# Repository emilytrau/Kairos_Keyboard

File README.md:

# Kairos_Keyboard
60% keyboard with MX-ALPS support and maximum compatability

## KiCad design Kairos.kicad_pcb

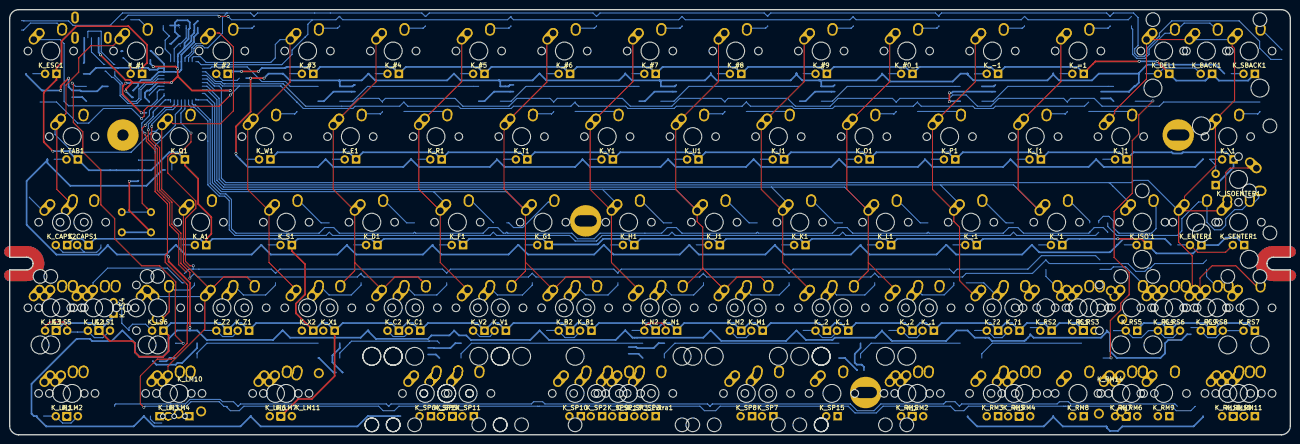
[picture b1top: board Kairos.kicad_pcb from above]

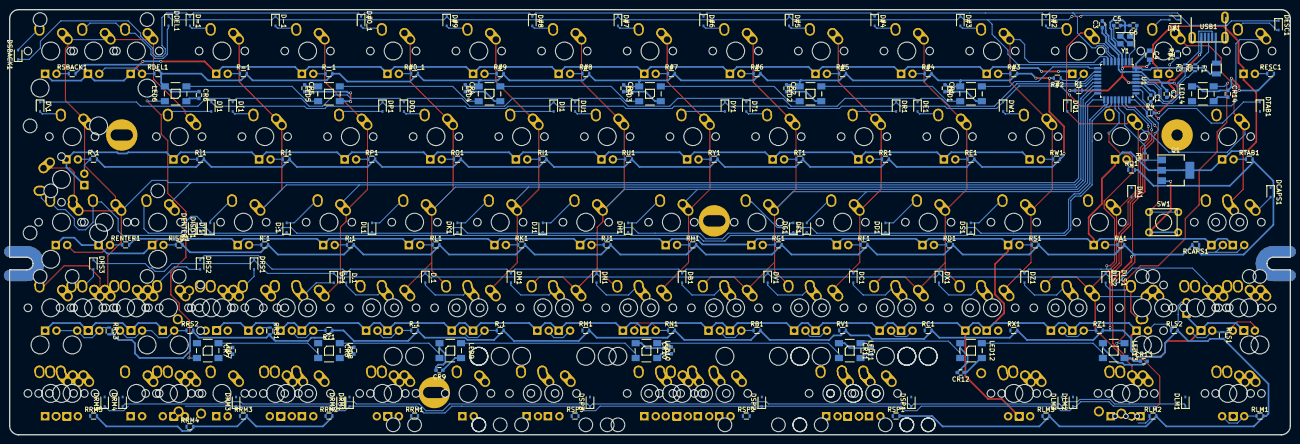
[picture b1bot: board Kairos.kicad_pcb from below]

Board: 2 copper layers, 285.0 x 94.6 mm, 300 parts (183 on the bottom side), 185 nets.

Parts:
C1: 1uF; C_0603
C2, C3: 100nF; C_0603
C4: 4.7uF; C_0805
C5, C6: 22pF; C_0603
CR1, CR2, CR3, CR4, CR5, CR6, CR7, CR8, CR9, CR10, CR11, CR12, CR13, CR14: 100nF; C_0603
D#0_1, D#1, D#2, D#3, D#4, D#5, D#6, D#7, D#8, D#9: 1N4148WS; D_SOD-323
D'1: 1N4148WS; D_SOD-323
D,1: 1N4148WS; D_SOD-323
D-1: 1N4148WS; D_SOD-323
D.1: 1N4148WS; D_SOD-323
D;1: 1N4148WS; D_SOD-323
D=1: 1N4148WS; D_SOD-323
D?1: 1N4148WS; D_SOD-323
DA1: 1N4148WS; D_SOD-323
DB1: 1N4148WS; D_SOD-323
DC1: 1N4148WS; D_SOD-323
DCAPS1: 1N4148WS; D_SOD-323
DD1: 1N4148WS; D_SOD-323
DDEL1: 1N4148WS; D_SOD-323
DE1: 1N4148WS; D_SOD-323
DENTER1: 1N4148WS; D_SOD-323
DESC1: 1N4148WS; D_SOD-323
DF1: 1N4148WS; D_SOD-323
DG1: 1N4148WS; D_SOD-323
DH1: 1N4148WS; D_SOD-323
DI1: 1N4148WS; D_SOD-323
DISO`1: 1N4148WS; D_SOD-323
DJ1: 1N4148WS; D_SOD-323
DK1: 1N4148WS; D_SOD-323
DL1: 1N4148WS; D_SOD-323
DLM1, DLM2, DLM3: 1N4148WS; D_SOD-323
DLS1, DLS2: 1N4148WS; D_SOD-323
DM1: 1N4148WS; D_SOD-323
DN1: 1N4148WS; D_SOD-323
DO1: 1N4148WS; D_SOD-323
DP1: 1N4148WS; D_SOD-323
DQ1: 1N4148WS; D_SOD-323
DR1: 1N4148WS; D_SOD-323
DRM1, DRM2, DRM3, DRM4, DRM5: 1N4148WS; D_SOD-323
DRS1, DRS2, DRS3: 1N4148WS; D_SOD-323
DS1: 1N4148WS; D_SOD-323
DSBACK1: 1N4148WS; D_SOD-323
DSP1, DSP2, DSP3: 1N4148WS; D_SOD-323
DT1: 1N4148WS; D_SOD-323
DTAB1: 1N4148WS; D_SOD-323
DU1: 1N4148WS; D_SOD-323
DV1: 1N4148WS; D_SOD-323
DW1: 1N4148WS; D_SOD-323
DX1: 1N4148WS; D_SOD-323
DY1: 1N4148WS; D_SOD-323
DZ1: 1N4148WS; D_SOD-323
D[1: 1N4148WS; D_SOD-323
D\1: 1N4148WS; D_SOD-323
D]1: 1N4148WS; D_SOD-323
F1: Polyfuse; Fuse_SMD1206_Reflow
K_#0_1, K_#1, K_#2, K_#3, K_#4, K_#5, K_#6, K_#7, K_#8, K_#9: MX-1U
K_'1: MX-1U
K_,1: MX-1U-FLIPPED; MX-1U
K_,2: MX-1U
K_-1: MX-1U
K_.1: MX-1U-FLIPPED; MX-1U
K_.2: MX-1U
K_;1: MX-1U
K_=1: MX-1U
K_?1: MX-1U-FLIPPED; MX-1U
K_?2: MX-1U
K_A1: MX-1U
K_B1: MX-1U-FLIPPED; MX-1U
K_B2: MX-1U
K_BACK1: MX-2U
K_C1: MX-1U-FLIPPED; MX-1U
K_C2: MX-1U
K_CAPS1: MX-1.75U
K_CAPS2: MX-1.25U
K_D1: MX-1U
K_DEL1: MX-1U
K_E1: MX-1U
K_ENTER1: MX-2.25U
K_ESC1: MX-1U
K_F1: MX-1U
K_G1: MX-1U
K_H1: MX-1U
K_I1: MX-1U
K_ISOENTER1: MX-ISO-FLIPPED; MX-ISO-Combined
K_ISO`1: MX-1U
K_J1: MX-1U
K_K1: MX-1U
K_L1: MX-1U
K_LM1, K_LM6: MX-1.25U
K_LM2, K_LM7: MX-1.5U; MX-1.5U-FLIPPED
K_LM3: MX-1.25U; MX-1.25U-FLIPPED
K_LM4: MX-1U
K_LM10: MX-1.25U; ALPS-1.25U
K_LM11: MX-1.5U-FLIPPED; ALPS-1.5U
K_LS1: MX-2.25U-FLIPPED
K_LS2: MX-2U-FLIPPED; MX-2U
K_LS3, K_LS4, K_LS6: MX-1U
K_LS5: MX-1.25U; MX-1.25U-FLIPPED
K_M1: MX-1U-FLIPPED; MX-1U
K_M2: MX-1U
K_N1: MX-1U-FLIPPED; MX-1U
K_N2: MX-1U
K_O1: MX-1U
K_P1: MX-1U
K_Q1: MX-1U
K_R1: MX-1U
K_RM1, K_RM7, K_RM11: MX-1U
K_RM2, K_RM4, K_RM6, K_RM10: MX-1.25U; MX-1.25U-FLIPPED
K_RM3, K_RM8, K_RM9: MX-1U-FLIPPED; MX-1U
K_RM5, K_RM12: MX-1.5U
K_RM14: MX-1.25U; ALPS-1.25U
K_RS1, K_RS4, K_RS7: MX-1U-FLIPPED; MX-1U
K_RS2, K_RS5: MX-1.75U
K_RS3: MX-1.25U-FLIPPED
K_RS6: MX-2.75U-FLIPPED
K_RS8: MX-1.75U; MX-1.75U-FLIPPED
K_RS9: MX-2U
K_RS10: KEYSW; MX_100
K_S1: MX-1U
K_SBACK1: MX-1U
K_SENTER1: MX-1.25U; MX-1U
K_SP2: MX-6.25U; MX-6.25U-ReversedStabilizers
K_SP3: MX-7U; MX-7U-ReversedStabilizers
K_SP3_Extra1: MX-6U; MX-6U-7UOverlay
K_SP5: MX-2.75U; MX-2.75U-ReversedStabilizer
K_SP6: MX-2.25U-FLIPPED; MX-2.25U-ReversedStabilizer
K_SP7, K_SP14: MX-2.25U; MX-2.25U-ReversedStabilizer
K_SP8, K_SP11, K_SP15: MX-2.75U-FLIPPED; MX-2.75U-ReversedStabilizer
K_SP9, K_SP10: MX-1.25U-FLIPPED; MX-1.25U
K_SP13: MX-2U-FLIPPED; MX-2U-ReversedStabilizers-FLIPPED
K_T1: MX-1U
K_TAB1: MX-1.5U
K_U1: MX-1U
K_V1: MX-1U-FLIPPED; MX-1U
K_V2: MX-1U
K_W1: MX-1U
K_X1: MX-1U-FLIPPED; MX-1U
K_X2: MX-1U
K_Y1: MX-1U
K_Z1: MX-1U-FLIPPED; MX-1U
K_Z2: MX-1U
K_[1: MX-1U
K_\1: MX-1.5U
K_]1: MX-1U
LED1, LED2, LED3, LED4, LED5, LED6, LED7, LED8, LED9, LED10, LED11, LED12, LED13, LED14: WS2812B
Q1: NSS40301MZ4T1G; SOT-223-3Lead_TabPin2
R1, R4: 10k; R_0603
R2, R3: 22; R_0603
R5: 1.5k; R_0603
R#0_1, R#1, R#2, R#3, R#4, R#5, R#6, R#7, R#8, R#9: 2.2k; R_0603
R'1: 2.2k; R_0603
R,1: 2.2k; R_0603
R-1: 2.2k; R_0603
R.1: 2.2k; R_0603
R;1: 2.2k; R_0603
R=1: 2.2k; R_0603
R?1: 2.2k; R_0603
RA1: 2.2k; R_0603
RB1: 2.2k; R_0603
RC1: 2.2k; R_0603
RCAPS1: 2.2k; R_0603
RD1: 2.2k; R_0603
RDEL1: 2.2k; R_0603
RE1: 2.2k; R_0603
RENTER1: 2.2k; R_0603
RESC1: 2.2k; R_0603
RF1: 2.2k; R_0603
RG1: 2.2k; R_0603
RH1: 2.2k; R_0603
RI1: 2.2k; R_0603
RISO`1: 2.2k; R_0603
RJ1: 2.2k; R_0603
RK1: 2.2k; R_0603
RL1: 2.2k; R_0603
RLM1, RLM2, RLM3: 2.2k; R_0603
RLS1, RLS2: 2.2k; R_0603
RM1: 2.2k; R_0603
RN1: 2.2k; R_0603
RO1: 2.2k; R_0603
RP1: 2.2k; R_0603
RQ1: 2.2k; R_0603
RR1: 2.2k; R_0603
RRM1, RRM2, RRM3, RRM4, RRM5: 2.2k; R_0603
RRS1, RRS2, RRS3: 2.2k; R_0603
RS1: 2.2k; R_0603
RSBACK1: 2.2k; R_0603
RSP1, RSP2, RSP3: 2.2k; R_0603
RT1: 2.2k; R_0603
RTAB1: 2.2k; R_0603
RU1: 2.2k; R_0603
RV1: 2.2k; R_0603
RW1: 2.2k; R_0603
RX1: 2.2k; R_0603
RY1: 2.2k; R_0603
RZ1: 2.2k; R_0603
R[1: 2.2k; R_0603
R\1: 2.2k; R_0603
R]1: 2.2k; R_0603
SW1: SW_RST1; PushButton_6x6mm_TH
U1: ATMEGA32U2-AU; TQFP-32_7x7mm_Pitch0.8mm
USB1: Molex-0548190589
Y1: Crystal_GND24; Crystal_SMD_3225-4pin_3.2x2.5mm

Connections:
+5V: C2.1, C3.1, C4.1, CR1.1, CR2.1, CR3.1, CR4.1, CR5.1, CR6.1, CR7.1, CR8.1, CR9.1, CR10.1, CR11.1, CR12.1, CR13.1, CR14.1, F1.1, LED1.1, LED2.1, LED3.1, LED4.1, LED5.1, LED6.1, LED7.1, LED8.1, LED9.1, LED10.1, LED11.1, LED12.1, LED13.1, LED14.1, R4.2, R#0_1.2, R#1.2, R#2.2, R#3.2, R#4.2, R#5.2, R#6.2, R#7.2, R#8.2, R#9.2, R'1.2, R,1.2, R-1.2, R.1.2, R;1.2, R=1.2, R?1.1, RA1.2, RB1.2, RC1.2, RCAPS1.2, RD1.2, RDEL1.2, RE1.2, RENTER1.2, RESC1.2, RF1.2, RG1.2, RH1.2, RI1.2, RISO`1.2, RJ1.2, RK1.2, RL1.2, RLM1.2, RLM2.2, RLM3.2, RLS1.2, RLS2.2, RM1.2, RN1.2, RO1.2, RP1.2, RQ1.2, RR1.2, RRM1.2, RRM2.2, RRM3.2, RRM4.2, RRM5.2, RRS1.2, RRS2.2, RRS3.2, RS1.2, RSBACK1.2, RSP1.2, RSP2.2, RSP3.2, RT1.2, RTAB1.2, RU1.2, RV1.2, RW1.2, RX1.2, RY1.2, RZ1.2, R[1.2, R\1.2, R]1.2, U1.4, U1.31, U1.32
COL0: K_ESC1.1, K_LM1.1, K_LM2.1, K_LS1.2, K_LS2.2, K_LS3.1, K_LS5.1, U1.26
COL1: K_#1.1, K_#2.1, K_A1.1, K_CAPS1.1, K_CAPS2.2, K_LM3.1, K_LM4.1, K_LM6.1, K_LM7.1, K_LM10.1, K_LM11.2, K_LS4.1, K_LS6.1, K_Q1.1, K_TAB1.1, K_Z1.2, K_Z2.1, U1.5
COL2: K_#3.1, K_#4.1, K_C1.2, K_C2.1, K_D1.1, K_E1.1, K_S1.1, K_W1.1, K_X1.2, K_X2.1, U1.7
COL3: K_#5.1, K_#6.1, K_B1.2, K_B2.1, K_F1.1, K_G1.1, K_R1.1, K_SP2.1, K_SP3.1, K_SP5.1, K_SP6.2, K_SP9.2, K_SP10.2, K_SP11.2, K_SP13.2, K_SP14.1, K_T1.1, K_V1.2, K_V2.1, U1.17
COL4: K_#7.1, K_#8.1, K_H1.1, K_J1.1, K_M1.2, K_M2.1, K_N1.2, K_N2.1, K_SP7.1, K_SP8.2, K_SP15.2, K_U1.1, K_Y1.1, U1.16
COL5: K_#0_1.1, K_#9.1, K_,1.2, K_,2.1, K_.1.2, K_.2.1, K_I1.1, K_K1.1, K_L1.1, K_O1.1, K_RM1.1, K_RM2.1, U1.15
COL6: K_'1.1, K_-1.1, K_;1.1, K_=1.1, K_?1.2, K_?2.1, K_P1.1, K_RM3.2, K_RM4.1, K_RM5.1, K_RM8.2, K_RS1.2, K_RS2.1, K_RS3.2, K_[1.1, U1.14
COL7: K_BACK1.1, K_DEL1.1, K_ENTER1.1, K_ISOENTER1.2, K_ISO`1.1, K_RM6.1, K_RM7.1, K_RM9.2, K_RM10.1, K_RM11.1, K_RM12.1, K_RM14.1, K_RS4.2, K_RS5.1, K_RS6.2, K_RS7.2, K_RS8.1, K_RS9.1, K_RS10.2, K_SBACK1.1, K_SENTER1.1, K_\1.1, K_]1.1, U1.12
DM: R3.2, USB1.4
DP: R2.2, USB1.3
GND: C1.2, C2.2, C3.2, C4.2, C5.2, C6.2, CR1.2, CR2.2, CR3.2, CR4.2, CR5.2, CR6.2, CR7.2, CR8.2, CR9.2, CR10.2, CR11.2, CR12.2, CR13.2, CR14.2, LED1.3, LED2.3, LED3.3, LED4.3, LED5.3, LED6.3, LED7.3, LED8.3, LED9.3, LED10.3, LED11.3, LED12.3, LED13.3, LED14.3, Q1.3, R1.1, SW1.1, U1.3, U1.28, USB1.1, Y1.2, Y1.4
LEDGND: K_#0_1.4, K_#1.4, K_#2.4, K_#3.4, K_#4.4, K_#5.4, K_#6.4, K_#7.4, K_#8.4, K_#9.4, K_'1.4, K_,1.4, K_,2.4, K_-1.4, K_.1.4, K_.2.4, K_;1.4, K_=1.4, K_?1.4, K_?2.4, K_A1.4, K_B1.4, K_B2.4, K_BACK1.4, K_C1.4, K_C2.4, K_CAPS1.4, K_CAPS2.4, K_D1.4, K_DEL1.4, K_E1.4, K_ENTER1.4, K_ESC1.4, K_F1.4, K_G1.4, K_H1.4, K_I1.4, K_ISOENTER1.4, K_ISO`1.4, K_J1.4, K_K1.4, K_L1.4, K_LM1.4, K_LM2.4, K_LM3.4, K_LM6.4, K_LM7.4, K_LS1.4, K_LS2.4, K_LS3.4, K_LS4.4, K_LS5.4, K_LS6.4, K_M1.4, K_M2.4, K_N1.4, K_N2.4, K_O1.4, K_P1.4, K_Q1.4, K_R1.4, K_RM1.4, K_RM2.4, K_RM3.4, K_RM4.4, K_RM5.4, K_RM6.4, K_RM7.4, K_RM8.4, K_RM9.4, K_RM10.4, K_RM11.4, K_RM12.4, K_RS1.4, K_RS2.4, K_RS3.4, K_RS4.4, K_RS5.4, K_RS6.4, K_RS7.4, K_RS8.4, K_RS9.4, K_S1.4, K_SBACK1.4, K_SENTER1.4, K_SP2.4, K_SP3.4, K_SP5.4, K_SP6.4, K_SP7.4, K_SP8.4, K_SP9.4, K_SP10.4, K_SP11.4, K_SP13.4, K_SP14.4, K_SP15.4, K_T1.4, K_TAB1.4, K_U1.4, K_V1.4, K_V2.4, K_W1.4, K_X1.4, K_X2.4, K_Y1.4, K_Z1.4, K_Z2.4, K_[1.4, K_\1.4, K_]1.4, Q1.2
unnamed: C1.1, U1.27
unnamed: C5.1, U1.2, Y1.3
unnamed: C6.1, U1.1, Y1.1
unnamed: D#0_1.2, K_#0_1.2
unnamed: D#1.2, K_#1.2
unnamed: D#2.2, K_#2.2
unnamed: D#3.2, K_#3.2
unnamed: D#4.2, K_#4.2
unnamed: D#5.2, K_#5.2
unnamed: D#6.2, K_#6.2
unnamed: D#7.2, K_#7.2
unnamed: D#8.2, K_#8.2
unnamed: D#9.2, K_#9.2
unnamed: D'1.2, K_'1.2
unnamed: D,1.2, K_,1.1, K_,2.2
unnamed: D-1.2, K_-1.2
unnamed: D.1.2, K_.1.1, K_.2.2
unnamed: D;1.2, K_;1.2
unnamed: D=1.2, K_=1.2
unnamed: D?1.2, K_?1.1, K_?2.2
unnamed: DA1.2, K_A1.2
unnamed: DB1.2, K_B1.1, K_B2.2
unnamed: DC1.2, K_C1.1, K_C2.2
unnamed: DCAPS1.2, K_CAPS1.2, K_CAPS2.1
unnamed: DD1.2, K_D1.2
unnamed: DDEL1.2, K_BACK1.2, K_DEL1.2
unnamed: DE1.2, K_E1.2
unnamed: DENTER1.2, K_ENTER1.2, K_ISOENTER1.1, K_SENTER1.2
unnamed: DESC1.2, K_ESC1.2
unnamed: DF1.2, K_F1.2
unnamed: DG1.2, K_G1.2
unnamed: DH1.2, K_H1.2
unnamed: DI1.2, K_I1.2
unnamed: DISO`1.2, K_ISO`1.2
unnamed: DJ1.2, K_J1.2
unnamed: DK1.2, K_K1.2
unnamed: DL1.2, K_L1.2
unnamed: DLM1.2, K_LM1.2, K_LM2.2
unnamed: DLM2.2, K_LM3.2, K_LM4.2, K_LM10.2
unnamed: DLM3.2, K_LM6.2, K_LM7.2, K_LM11.1
unnamed: DLS1.2, K_LS1.1, K_LS2.1, K_LS3.2, K_LS5.2
unnamed: DLS2.2, K_LS4.2, K_LS6.2
unnamed: DM1.2, K_M1.1, K_M2.2
unnamed: DN1.2, K_N1.1, K_N2.2
unnamed: DO1.2, K_O1.2
unnamed: DP1.2, K_P1.2
unnamed: DQ1.2, K_Q1.2
unnamed: DR1.2, K_R1.2
unnamed: DRM1.2, K_RM1.2, K_RM2.2
unnamed: DRM2.2, K_RM3.1, K_RM4.2, K_RM5.2
unnamed: DRM3.2, K_RM8.1
unnamed: DRM4.2, K_RM6.2, K_RM7.2, K_RM9.1, K_RM14.2
unnamed: DRM5.2, K_RM10.2, K_RM11.2, K_RM12.2
unnamed: DRS1.2, K_RS1.1, K_RS2.2, K_RS3.1
unnamed: DRS2.2, K_RS4.1, K_RS5.2, K_RS6.1, K_RS10.1
unnamed: DRS3.2, K_RS7.1, K_RS8.2, K_RS9.2
unnamed: DS1.2, K_S1.2
unnamed: DSBACK1.2, K_SBACK1.2
unnamed: DSP1.2, K_SP5.2, K_SP6.1, K_SP11.1, K_SP14.2
unnamed: DSP2.2, K_SP2.2, K_SP3.2, K_SP9.1, K_SP10.1, K_SP13.1
unnamed: DSP3.2, K_SP7.2, K_SP8.1, K_SP15.1
unnamed: DT1.2, K_T1.2
unnamed: DTAB1.2, K_TAB1.2
unnamed: DU1.2, K_U1.2
unnamed: DV1.2, K_V1.1, K_V2.2
unnamed: DW1.2, K_W1.2
unnamed: DX1.2, K_X1.1, K_X2.2
unnamed: DY1.2, K_Y1.2
unnamed: DZ1.2, K_Z1.1, K_Z2.2
unnamed: D[1.2, K_[1.2
unnamed: D\1.2, K_\1.2
unnamed: D]1.2, K_]1.2
unnamed: K_#0_1.3, R#0_1.1
unnamed: K_#1.3, R#1.1
unnamed: K_#2.3, R#2.1
unnamed: K_#3.3, R#3.1
unnamed: K_#4.3, R#4.1
unnamed: K_#5.3, R#5.1
unnamed: K_#6.3, R#6.1
unnamed: K_#7.3, R#7.1
unnamed: K_#8.3, R#8.1
unnamed: K_#9.3, R#9.1
unnamed: K_'1.3, R'1.1
unnamed: K_,1.3, K_,2.3, R,1.1
unnamed: K_-1.3, R-1.1
unnamed: K_.1.3, K_.2.3, R.1.1
unnamed: K_;1.3, R;1.1
unnamed: K_=1.3, R=1.1
unnamed: K_?1.3, K_?2.3, R?1.2
unnamed: K_A1.3, RA1.1
unnamed: K_B1.3, K_B2.3, RB1.1
unnamed: K_BACK1.3, K_DEL1.3, RDEL1.1
unnamed: K_C1.3, K_C2.3, RC1.1
unnamed: K_CAPS1.3, K_CAPS2.3, RCAPS1.1
unnamed: K_D1.3, RD1.1
unnamed: K_E1.3, RE1.1
unnamed: K_ENTER1.3, K_SENTER1.3, RENTER1.1
unnamed: K_ESC1.3, RESC1.1
unnamed: K_F1.3, RF1.1
unnamed: K_G1.3, RG1.1
unnamed: K_H1.3, RH1.1
unnamed: K_I1.3, RI1.1
unnamed: K_ISOENTER1.3, K_\1.3, R\1.1
unnamed: K_ISO`1.3, RISO`1.1
unnamed: K_J1.3, RJ1.1
unnamed: K_K1.3, RK1.1
unnamed: K_L1.3, RL1.1
unnamed: K_LM1.3, K_LM2.3, RLM1.1
unnamed: K_LM3.3, K_LM4.3, RLM2.1
unnamed: K_LM6.3, K_LM7.3, RLM3.1
unnamed: K_LS1.3, K_LS2.3, K_LS3.3, K_LS5.3, RLS1.1
unnamed: K_LS4.3, K_LS6.3, RLS2.1
unnamed: K_M1.3, K_M2.3, RM1.1
unnamed: K_N1.3, K_N2.3, RN1.1
unnamed: K_O1.3, RO1.1
unnamed: K_P1.3, RP1.1
unnamed: K_Q1.3, RQ1.1
unnamed: K_R1.3, RR1.1
unnamed: K_RM1.3, K_RM2.3, RRM1.1
unnamed: K_RM3.3, K_RM4.3, K_RM5.3, RRM2.1
unnamed: K_RM8.3, RRM3.1
unnamed: K_RM10.3, K_RM11.3, K_RM12.3, RRM5.1
unnamed: K_RM6.3, K_RM7.3, K_RM9.3, RRM4.1
unnamed: K_RS1.3, K_RS2.3, K_RS3.3, RRS1.1
unnamed: K_RS4.3, K_RS5.3, K_RS6.3, RRS2.1
unnamed: K_RS7.3, K_RS8.3, K_RS9.3, RRS3.1
unnamed: K_S1.3, RS1.1
unnamed: K_SBACK1.3, RSBACK1.1
unnamed: K_SP2.3, K_SP3.3, K_SP9.3, K_SP10.3, K_SP13.3, RSP2.1
unnamed: K_SP5.3, K_SP6.3, K_SP11.3, K_SP14.3, RSP1.1
unnamed: K_SP7.3, K_SP8.3, K_SP15.3, RSP3.1
unnamed: K_T1.3, RT1.1
unnamed: K_TAB1.3, RTAB1.1
unnamed: K_U1.3, RU1.1
unnamed: K_V1.3, K_V2.3, RV1.1
unnamed: K_W1.3, RW1.1
unnamed: K_X1.3, K_X2.3, RX1.1
unnamed: K_Y1.3, RY1.1
unnamed: K_Z1.3, K_Z2.3, RZ1.1
unnamed: K_[1.3, R[1.1
unnamed: K_]1.3, R]1.1
unnamed: LED1.2, LED2.4
unnamed: LED2.2, LED3.4
unnamed: LED3.2, LED4.4
unnamed: LED4.2, LED5.4
unnamed: LED5.2, LED6.4
unnamed: LED6.2, LED7.4
unnamed: LED7.2, LED8.4
unnamed: LED8.2, LED9.4
unnamed: LED10.2, LED11.4
unnamed: LED9.2, LED10.4
unnamed: LED11.2, LED12.4
unnamed: LED12.2, LED13.4
unnamed: LED13.2, LED14.4
unnamed: Q1.1, R5.1
unnamed: R1.2, U1.13
unnamed: R2.1, U1.29
unnamed: R3.1, U1.30
unnamed: R4.1, SW1.2, U1.24
unnamed: R5.2, U1.21
RGBLED: LED1.4, U1.9
ROW0: D#0_1.1, D#2.1, D#4.1, D#6.1, D#8.1, D=1.1, DESC1.1, DSBACK1.1, U1.6
ROW1: D#1.1, D#3.1, D#5.1, D#7.1, D#9.1, D-1.1, DDEL1.1, U1.8
ROW2: DE1.1, DO1.1, DQ1.1, DT1.1, DU1.1, D[1.1, D\1.1, U1.10
ROW3: DI1.1, DP1.1, DR1.1, DTAB1.1, DW1.1, DY1.1, D]1.1, U1.11
ROW4: D'1.1, DA1.1, DD1.1, DENTER1.1, DG1.1, DJ1.1, DL1.1, U1.18
ROW5: D;1.1, DCAPS1.1, DF1.1, DH1.1, DISO`1.1, DK1.1, DS1.1, U1.19
ROW6: D.1.1, DB1.1, DC1.1, DLS1.1, DM1.1, DRS2.1, DZ1.1, U1.20
ROW7: D,1.1, D?1.1, DLS2.1, DN1.1, DRS1.1, DRS3.1, DV1.1, DX1.1, U1.22
ROW8: DLM1.1, DLM3.1, DRM2.1, DRM4.1, DSP1.1, DSP3.1, U1.23
ROW9: DLM2.1, DRM1.1, DRM3.1, DRM5.1, DSP2.1, U1.25
VCC: F1.2, USB1.5

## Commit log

2017-05-14 Create project
2017-05-14 Setup
2017-05-14 Fix directory issues for schematic libs
    Whoops
2017-05-14 ATMEGA circuit
    Just the bare basics.
2017-05-14 Add a few things
2017-05-14 Hope this submodule thing works
2017-05-14 Redirect library and components directories to submodule
    Hope this works
2017-05-14 Testing WS2812B Submodule
2017-05-14 WS2812B Wiring and libs
2017-05-14 Progress
2017-05-14 Whoops
    Forgot RGB Decoup Caps
2017-05-15 Schema changes
2017-05-15 Row 1
2017-05-15 Row 2
2017-05-15 4 Rows + Hierarchial sheets for complex areas
2017-05-15 Finish Left Shift cluster
    Done.
2017-05-15 Whoops
2017-05-15 Finish up Left Shift
    Fix LED pinout reversed keys
2017-05-15 Change Left Shift key names
    Also synced the source to external backup in case GitHub breaks
2017-05-16 Finish up doubled 1U switches on the 2nd from bottom row
2017-05-16 Prepare for other complex footprint areas
2017-05-16 More work
2017-05-16 Updated submodule version
2017-05-16 Linked component library
2017-05-17 Update component library
2017-05-17 Cleaned up left shift
2017-05-17 Added spacebar schematic
2017-05-17 Added reference diagram
2017-05-18 Named alpha key diodes
2017-05-18 Clean up left shift
2017-05-18 Updated component labels
2017-05-18 Added left modifiers to schematic
2017-05-18 Added right shift to schematic
2017-05-21 Finish up columns on main matrix
2017-05-21 Finish Main Matrix
2017-05-21 Updated layout tracking
2017-05-22 Some edits
2017-05-27 LED portion of main matrix, bug fixes
    Add junctions which need to exist
2017-05-27 Finish Spacebar Routing
2017-05-30 Added row/col labels
2017-05-30 Fixed left shift
2017-06-02 Added left mods to matrix
2017-06-02 Hooked up right shift to matrix
2017-06-02 Switched matrix to global labels
2017-06-02 Added right mods
2017-06-02 Fixed spacebar
2017-06-18 Add USB
    USB connector and PTC fuse for 5V
2017-06-18 Add in the 60% footprint
2017-06-18 Update annotations
2017-06-18 Link more submodules
2017-06-18 Add reset button, link libs
2017-06-18 Some minor edits
2017-06-18 Swap USB connector lib
2017-06-18 Fix alphazero
2017-06-18 Change first row annotations
    More to be completed soon
2017-06-18 Fix annotations for secondary sheet
2017-06-18 Fix all key annotations
2017-06-18 Fix left shift, associate MX footprints
2017-06-18 Finish row 1
2017-06-18 Finish row 2
2017-06-18 Row 3
    We're missing 1.25U for split enter
2017-06-20 Added PCB outline
2017-06-20 Laid out PCB
2017-06-20 Change outline
2017-06-20 New associations for controller parts
2017-06-20 Associate USB parts
2017-06-20 The ATMega has landed
2017-06-20 Syyync
2017-06-20 Update layout
2017-06-20 Rotated ISO enter stabs
2017-06-20 Added ? key
2017-06-20 Added stepped caps lock
2017-06-20 Added most spacebar schematics
2017-06-20 Updated submodule
2017-06-20 Fix associations and netlist
2017-06-20 Revert "Fix associations and netlist"
    This reverts commit 3097880a18e80cee9ea6b621c2d5dbab02aaad42.
2017-06-20 Added spacebars - need sorting
2017-06-20 Renamed left mods
2017-06-21 Removed duplicate space bars
2017-06-21 added split enter
2017-06-21 more left mods added
2017-06-26 Update associations for transistor and TQFP-ify the controller
2017-06-26 Add missing 1.5k resistor on LED PWM
2017-06-26 Seems like the crystal pinout is incorrect
    Commit before fix for the sake of safety
2017-06-26 Fix the crystal
2017-06-26 Finish controller area
    Poof
2017-07-06 Prepare for layout checking
    Add updated layout screenshot
2017-07-07 Adjust transistor location
    Last one was too close to board edge
2017-07-07 Breakout Left Shift to match diagram
2017-07-07 Breakout row 2 and right shift to match diagram
2017-07-09 Added more right shift layouts
2017-07-09 Halfway fix RS2
    Failed to load cvpcb
2017-07-09 Fix RS2
2017-07-26 Changed led hole shape
2017-07-30 Unroute some stuff for repositioning
2017-07-30 Second attempt at controller area
    Cleaned up some circuitry and placement
2017-07-30 Unroute crystal for re-organization
2017-07-30 Crystal Take 2
    Still not satisfactory, but better
2017-07-30 Finalize controller area
2017-07-30 Move transistor
2017-07-30 Test breakout to make sure it's possible
2017-07-30 Begin rework of schematic
2017-07-30 Erase the schematic main grid
    Clean slate
2017-07-30 Clone a bunch of keys
2017-07-30 Rebuild key placement, unwired
2017-07-30 Rename some more keys
    Saving just in case
2017-07-30 Rename 2nd row keys
2017-07-30 Rename 3rd row
2017-07-30 Finish renaming keys
    Now onto resistors
2017-07-30 Rename first row of resistors
2017-07-30 Rename first row diodes
2017-07-30 Rename all resistors
2017-07-30 Rename diodes
2017-07-30 Wire cols
2017-07-30 Increase sheet size
    Components were falling off the edge
2017-07-30 Wire LEDGND
2017-07-30 Wire rows
2017-07-30 Wire the LEDs + Some cleanup with connections
2017-07-30 Finalization
2017-07-30 Fix left shift diode location
2017-07-30 Fix left mods diode location
2017-07-30 Revert "Fix left mods diode location"
    This reverts commit 3448258528d86bfc7727b0cdfdec81eb2e658ed9.
2017-07-30 Revert "Fix left shift diode location"
    This reverts commit 056763cd58f98b81803ed1bf762ad7910100d5c7.
2017-07-30 Add ISO/Small Enter, Update netlist
2017-07-30 Read updated netlist
2017-08-05 Fix up the controller a bit
    Move some parts away from nearby pads
2017-08-05 Test add submodule usb
2017-08-05 Add lib, update schematic
2017-08-05 Add footprint lib
2017-08-05 Generate new netlist
2017-08-05 Add that USB port
    Not placed correctly yet
2017-08-06 Place and wire Mini-USB connector
2017-08-06 Move some components
2017-08-06 Fix caps wiring and update netlist
2017-08-06 Update submodules
2017-08-06 Add reset button
    Unlocked outline footprint to measure dimensions
2017-08-06 Fix LShift Diode Location
2017-08-06 Fix LMods Diode Location
2017-08-06 Fix RMods Diode Location
2017-08-06 Fix RShift Diode Location
2017-08-06 Update Netlist
2017-08-06 Read new netlist
2017-08-06 Begin reassembly of keys
    left shift
2017-08-06 Recombine keys
2017-08-06 Revert "Recombine keys"
    This reverts commit 2512aeec9bc2357bde49aae56887a85b5ab5ed56.
2017-08-06 Revert "Begin reassembly of keys"
    This reverts commit c9b45bfa7da2bb3e248b17a6d2062ef67b7d9814.
2017-08-06 Relock outline, unlock a switch
    No idea why one of the regular 1U were locked after being broken out
2017-08-06 Flip some spacebars
2017-08-06 Flip again since KiCad ignored changes
2017-08-06 Add dummy 6U hole schematic
2017-08-06 Stack bottom row, move HHKB layout out of the way temporarily
2017-08-06 Move stock XD60 layout (+SP3 7U) to main layout
2017-08-06 Stack shift row
2017-08-06 Label excluded keys for prioritization
2017-08-06 Update submodules yet again
2017-08-06 Fix 2.25 and 2.75U flipped stabilizer holes
2017-08-06 Get rid of LM5 and SP1 for 6.5U bottom row
2017-08-06 Remove the two keys on PCB
2017-08-06 Remove true HHKB row (LM8/9, SP15, RM15/16)
2017-08-06 Prepare for switch location testing
2017-08-06 Remove RM17, RM18
2017-08-06 Remove SP14, clean up PCB
2017-08-06 Fix first batch of wrong size footprints
2017-08-06 Fix wrong size footprints (Hopefully all of them)
2017-08-06 Update outline to latest
2017-08-06 Fixed most led positions
2017-08-08 Add 7U Split Spacebar
2017-08-08 Reverse order in schematic, load changes
2017-08-08 Flip 7U Split order, change SP13 to 2U for stabilizer holes
2017-08-08 Done
2017-08-08 Add in the Alps bottom row
2017-08-08 Add 2 more RGBs and their decoupling caps
2017-08-08 Add in the RGBs to PCB (Not organized yet)
2017-08-08 Place the RGBs in reasonable locations
2017-08-08 Place RGB Decoupling Caps
2017-08-08 Add spacebar diodes
2017-08-08 Assign the footprints for every resistor and diode
2017-08-08 Load in all the components on PCB
2017-08-08 Wire the RGB Data lines
2017-08-08 Remove some traces for organization
2017-08-08 Some progress in wiring
2017-08-08 Mark pinout
2017-08-08 Bus routed
2017-08-08 Wire cols and place some diodes
2017-08-11 Flipped schematic symbols for keys (except LS and bottom right mods)
2017-08-11 Minor change to bus wiring
2017-08-13 Flipped led footprints
2017-08-13 Remove temp library
2017-08-13 Added new right shift layout and rotated ISO stabs
2017-08-13 Fixed conflict on left shift key
2017-08-13 Update outline
2017-08-16 Placed diodes in preliminary positions
2017-08-16 Wired up most diodes to rows
2017-08-16 Placed resistors in preliminary positions
2017-08-20 Wired some leds
2017-08-28 A few LEDs under right shift
2017-08-28 A few LED power lines on bottom row
2017-08-28 Some more LED related traces
2017-08-28 Various wiring and repairing near controller
2017-08-28 Wire the isolated LEDGND pin on 2nd key
2017-08-28 Reposition the decoupling caps of the RGB LEDs
2017-09-16 A bit of progress
    Waiting for college to calm down
